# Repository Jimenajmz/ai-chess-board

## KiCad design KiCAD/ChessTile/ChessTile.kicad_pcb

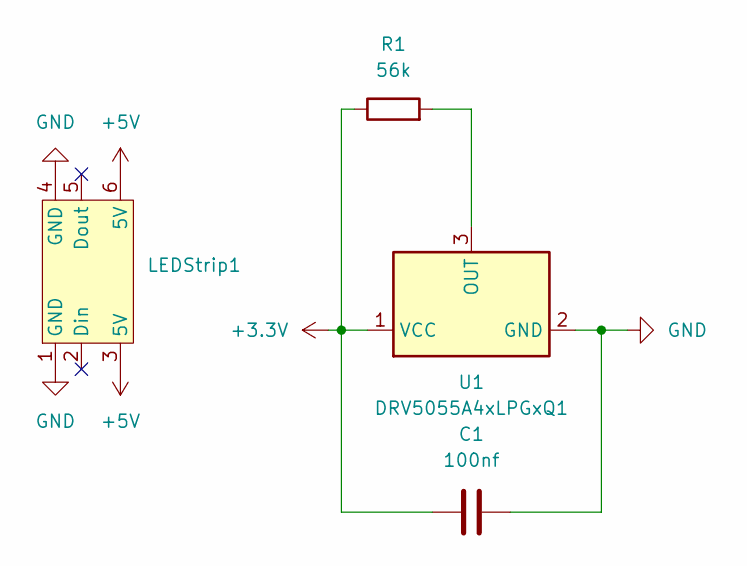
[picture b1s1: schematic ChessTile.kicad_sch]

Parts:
C1: 100nf; C_Axial_L3.8mm_D2.6mm_P7.50mm_Horizontal
LEDStrip1: ws2812bLEDStrip
R1: 56k; R_Axial_DIN0207_L6.3mm_D2.5mm_P7.62mm_Horizontal
U1: DRV5055A4xLPGxQ1; TO-92_HandSolder

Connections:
+3.3V: C1.1, R1.1, U1.1 (VCC)
+5V: LEDStrip1.3 (5V), LEDStrip1.6 (5V)
GND: C1.2, LEDStrip1.1 (GND), LEDStrip1.4 (GND), U1.2 (GND)
unnamed: R1.2, U1.3 (OUT)

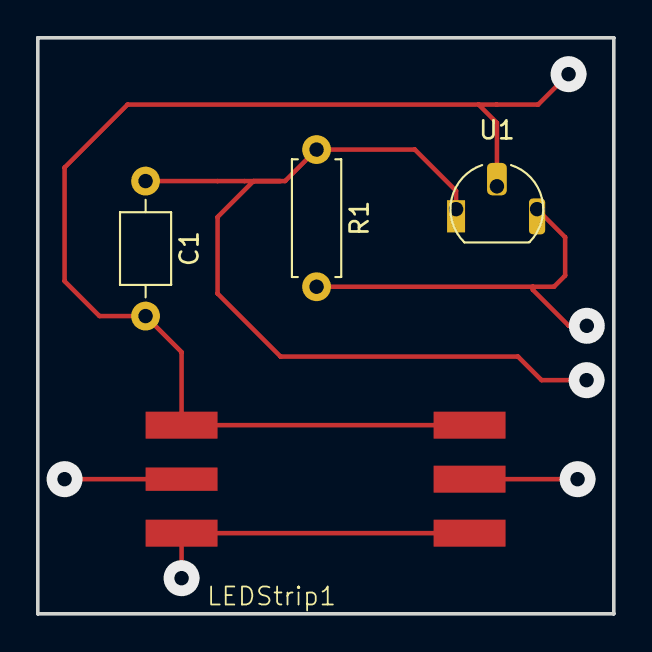
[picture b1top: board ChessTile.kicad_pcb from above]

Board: 2 copper layers, 32.0 x 32.0 mm, 4 parts (0 on the bottom side), 4 nets.

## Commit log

2024-07-27 Added test script for the PCBs and KiCAD PCB
